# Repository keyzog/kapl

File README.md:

# Kapl Keyboard

The Kapl is a split ergonomic keyboard with 70 keys (7x5).
Please read project wiki for details: https://github.com/keyzog/kapl/wiki

**Detailed assembly instructions:** https://keyzog.com/post/kapl-build-guide (RU)

Board with controller on back side.

## PCB

[gerbers/gerber\_\_main.zip](https://github.com/keyzog/kapl/raw/main/gerbers/gerber__main.zip)

## Firmware

Kapl uses [QMK firmware](https://qmk.fm/)

## Todo

-  [x] [list of materials](https://github.com/keyzog/kapl/wiki#bill-of-materials)
-  [x] rotation encoder support
-  [ ] building guide
-  [ ] tilting-tenting case

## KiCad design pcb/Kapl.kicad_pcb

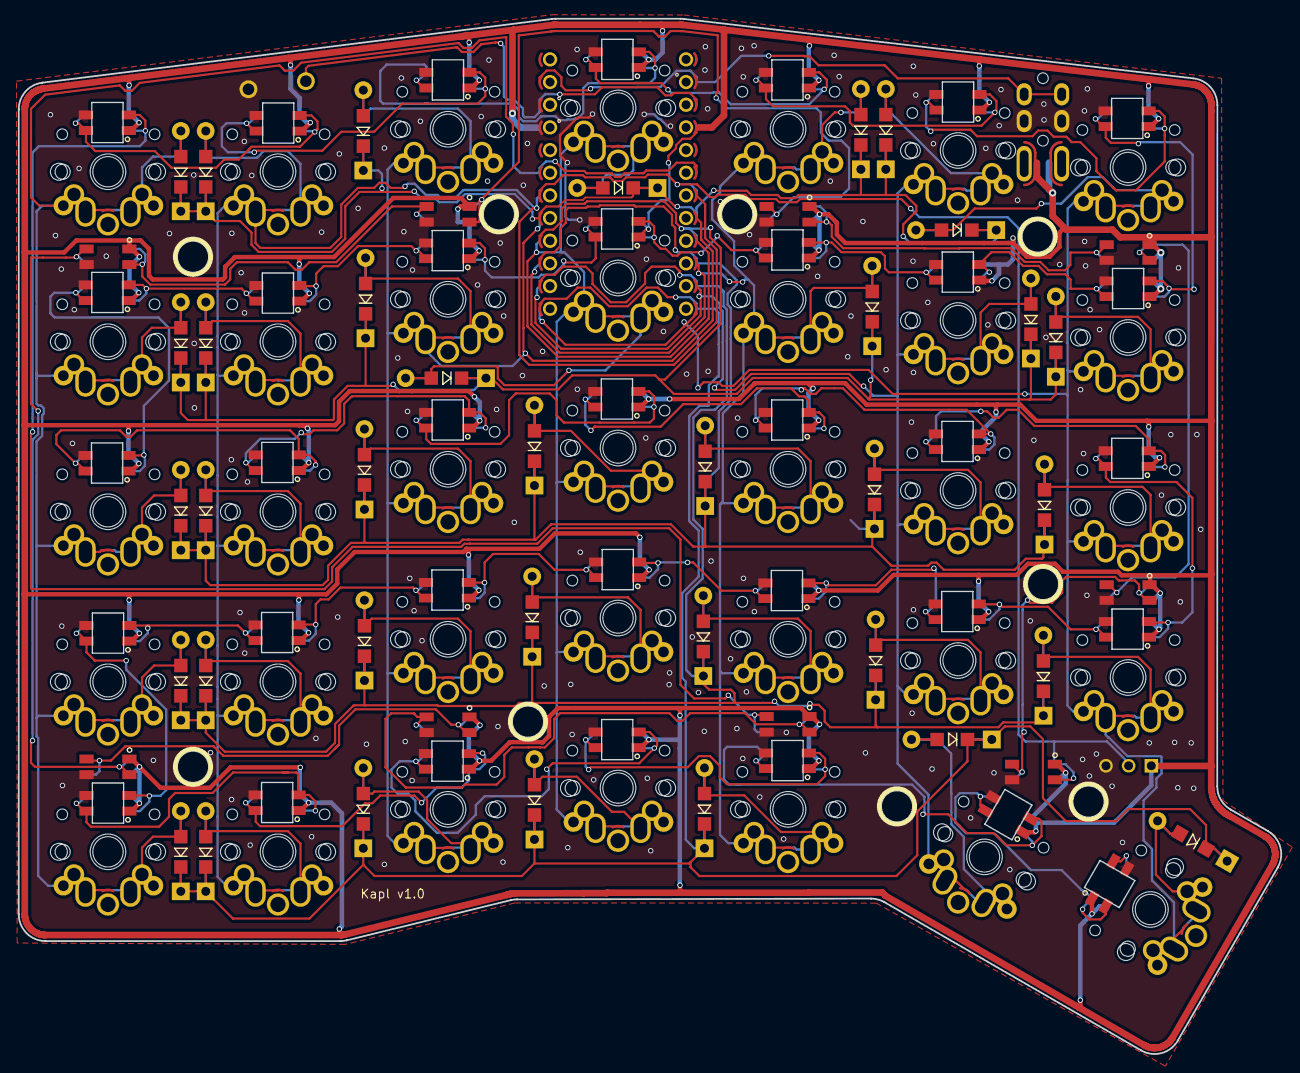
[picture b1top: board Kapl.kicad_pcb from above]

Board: 2 copper layers, 141.5 x 116.0 mm, 127 parts (0 on the bottom side), 95 nets.

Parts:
BL1, BL2, BL3, BL4, BL5, BL6, BL7, BL8, BL9: SK6812MINI; SK6812MINI_surface
D1, D2, D3, D4, D5, D6, D7, D8, D9, D10, D11, D12, D13, D14, D15, D16, D17, D18, D19, D20, D21, D22, D23, D24, D25, D26, D27, D28, D29, D30, D31, D32, D33, D34, D35: D; Diode
H1, H2, H3, H4, H5, H6, H7, H8, H9: MountingHole; MountingHole_3.2mm_M3
J1: LED_strip_conector; StripLED_rev
L1, L2, L3, L4, L5, L6, L7, L8, L9, L10, L11, L12, L13, L14, L15, L16, L17, L18, L19, L20, L21, L22, L23, L24, L25, L26, L27, L28, L29, L30, L31, L32, L33, L34, L35: SK6812MINI; SK6812MINI_rev
MJ1: Mini Jack; MJ-4PP-9
RSW1: SW_PUSH; ResetSW
SW1, SW2, SW3, SW4, SW5, SW6, SW7, SW8, SW9, SW10, SW11, SW12, SW13, SW14, SW15, SW16, SW17, SW18, SW19, SW20, SW21, SW22, SW23, SW24, SW25, SW26, SW27, SW28, SW29, SW30, SW31, SW32, SW33, SW34, SW35: SW_PUSH; MX-ALPs-PG1350-rev
U1: ProMicro

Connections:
GND: BL1.2, BL2.2, BL3.2, BL4.2, BL5.2, BL6.2, BL7.2, BL8.2, BL9.2, J1.1, L1.2, L2.2, L3.2, L4.2, L5.2, L6.2, L7.2, L8.2, L9.2, L10.2, L11.2, L12.2, L13.2, L14.2, L15.2, L16.2, L17.2, L18.2, L19.2, L20.2, L21.2, L22.2, L23.2, L24.2, L25.2, L26.2, L27.2, L28.2, L29.2, L30.2, L31.2, L32.2, L33.2, L34.2, L35.2, MJ1.C, RSW1.2, U1.3, U1.4, U1.23
LED: BL1.3, J1.2, U1.7
unnamed: BL1.1, BL2.3
unnamed: BL2.1, BL3.3
unnamed: BL3.1, BL4.3
unnamed: BL4.1, BL5.3
unnamed: BL5.1, BL6.3
unnamed: BL6.1, BL7.3
unnamed: BL7.1, BL8.3
unnamed: BL8.1, BL9.3
unnamed: BL9.1, L1.3
unnamed: D1.2, SW1.2
unnamed: D2.2, SW2.2
unnamed: D3.2, SW3.2
unnamed: D4.2, SW4.2
unnamed: D5.2, SW5.2
unnamed: D6.2, SW6.2
unnamed: D7.2, SW7.2
unnamed: D8.2, SW8.2
unnamed: D9.2, SW9.2
unnamed: D10.2, SW10.2
unnamed: D11.2, SW11.2
unnamed: D12.2, SW12.2
unnamed: D13.2, SW13.2
unnamed: D14.2, SW14.2
unnamed: D15.2, SW15.2
unnamed: D16.2, SW16.2
unnamed: D17.2, SW17.2
unnamed: D18.2, SW18.2
unnamed: D19.2, SW19.2
unnamed: D20.2, SW20.2
unnamed: D21.2, SW21.2
unnamed: D22.2, SW22.2
unnamed: D23.2, SW23.2
unnamed: D24.2, SW24.2
unnamed: D25.2, SW25.2
unnamed: D26.2, SW26.2
unnamed: D27.2, SW27.2
unnamed: D28.2, SW28.2
unnamed: D29.2, SW29.2
unnamed: D30.2, SW30.2
unnamed: D31.2, SW31.2
unnamed: D32.2, SW32.2
unnamed: D33.2, SW33.2
unnamed: D34.2, SW34.2
unnamed: D35.2, SW35.2
unnamed: L1.1, L2.3
unnamed: L2.1, L3.3
unnamed: L3.1, L4.3
unnamed: L4.1, L5.3
unnamed: L5.1, L6.3
unnamed: L6.1, L7.3
unnamed: L8.3, L9.1
unnamed: L9.3, L10.1
unnamed: L10.3, L11.1
unnamed: L11.3, L12.1
unnamed: L12.3, L13.1
unnamed: L13.3, L14.1
unnamed: L7.1, L14.3
unnamed: L15.1, L16.3
unnamed: L8.1, L15.3
unnamed: L16.1, L17.3
unnamed: L17.1, L18.3
unnamed: L18.1, L19.3
unnamed: L19.1, L20.3
unnamed: L20.1, L21.3
unnamed: L21.1, L28.3
unnamed: L22.1, L29.3
unnamed: L22.3, L23.1
unnamed: L23.3, L24.1
unnamed: L24.3, L25.1
unnamed: L25.3, L26.1
unnamed: L26.3, L27.1
unnamed: L27.3, L28.1
unnamed: L29.1, L30.3
unnamed: L30.1, L31.3
unnamed: L31.1, L32.3
unnamed: L32.1, L33.3
unnamed: L33.1, L34.3
unnamed: L34.1, L35.3
VCC: BL1.4, BL2.4, BL3.4, BL4.4, BL5.4, BL6.4, BL7.4, BL8.4, BL9.4, J1.3, L1.4, L2.4, L3.4, L4.4, L5.4, L6.4, L7.4, L8.4, L9.4, L10.4, L11.4, L12.4, L13.4, L14.4, L15.4, L16.4, L17.4, L18.4, L19.4, L20.4, L21.4, L22.4, L23.4, L24.4, L25.4, L26.4, L27.4, L28.4, L29.4, L30.4, L31.4, L32.4, L33.4, L34.4, L35.4, MJ1.D, U1.21
col0: SW1.1, SW8.1, SW15.1, SW22.1, SW29.1, U1.19
col1: SW2.1, SW9.1, SW16.1, SW23.1, SW30.1, U1.18
col2: SW3.1, SW10.1, SW17.1, SW24.1, SW31.1, U1.17
col3: SW4.1, SW11.1, SW18.1, SW25.1, SW32.1, U1.16
col4: SW5.1, SW12.1, SW19.1, SW26.1, SW33.1, U1.15
col5: SW6.1, SW13.1, SW20.1, SW27.1, SW34.1, U1.14
col6: SW7.1, SW14.1, SW21.1, SW28.1, SW35.1, U1.13
data: MJ1.B, U1.2
reset: RSW1.1, U1.22
row0: D1.1, D2.1, D3.1, D4.1, D5.1, D6.1, D7.1, U1.8
row1: D8.1, D9.1, D10.1, D11.1, D12.1, D13.1, D14.1, U1.9
row2: D15.1, D16.1, D17.1, D18.1, D19.1, D20.1, D21.1, U1.10
row3: D22.1, D23.1, D24.1, D25.1, D26.1, D27.1, D28.1, U1.11
row4: D29.1, D30.1, D31.1, D32.1, D33.1, D34.1, D35.1, U1.12

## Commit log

2022-02-03 Fix links
2022-02-07 corrected a typo
2022-05-20 Create LICENSE
2023-01-27 update pcb v1.1
    - added rotation encoder support
    - changed controller's jumpers
2023-01-28 add bottom and top plates
2023-01-28 add new gerbers
2023-01-30 little changes in pcbs
2023-01-30 new gerbers
2023-02-06 get back old kicad files for main PCB 🙃
2023-02-06 remove gerber 1.1 from this branch🙃
2023-02-06 rename main pcb gerber file
2023-02-06 add directory for "cases" and move case kicad files to case/pcb
2023-02-06 add bottom pcb cases different types
2023-02-06 move case gerbers
2023-02-06 add pics
2023-02-06 Pcb rev (#3)
    * update pcb v1.1
    - added rotation encoder support
    - changed controller's jumpers
    * add bottom and top plates
    * add new gerbers
    * little changes in pcbs
2023-02-06 change path to pcb gerber
2023-05-01 add new image
2023-06-28 update pcb
2023-06-28 add images for Acrylic Case
2023-06-28 update leds_pins image
2023-06-28 move dxf files in case dir
2023-06-28 rename bottom dxf file
2023-06-28 add leds strip image
2023-06-28 change README
2023-06-28 update pcb image
